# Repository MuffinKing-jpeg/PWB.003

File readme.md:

# PWB.003

PCB for powering something from 1S LI-PO or USB.  
Uses PMIC with integrated power mux.

Schematics: [Schematics](plots/PWB.003.pdf)  
Mechanical: [Mechanical](plots/PWB.003__Assembly.pdf)  
BOM: [BOM](production/bom.csv)

## Key features

- Configurable output
- Up to 3.5A input
- 2.5v\<VOUT\<16v
- Battery charging and protection
- low quiescent power consumption (In theory, still not tested)
- OVP, OCP, UVP (as claimed in datasheet for BQ24073RGT)

## Connectors

- 5x1 P1.25 for control communication with MCU
- 1x4 P2.54 for powering directly from BMS and measuring battery voltage
- 1x3 P2.00 for connecting LI-PO
- XT30 for input from battery
- XT30 for output after buck-bust
- USB-C for charging

## Key components

- BQ24073RGT
- TPS63070RNMR

## Test results

TBD

## Photos

## Disclaimer

This hardware design is provided "as is", without warranty of any kind, express or implied, including but not limited to the warranties of merchantability, fitness for a particular purpose, or noninfringement. The authors are not responsible for any damages, losses, or issues caused by the use of this design.

You are responsible for ensuring that the design complies with local regulations, safety standards, and any applicable laws.

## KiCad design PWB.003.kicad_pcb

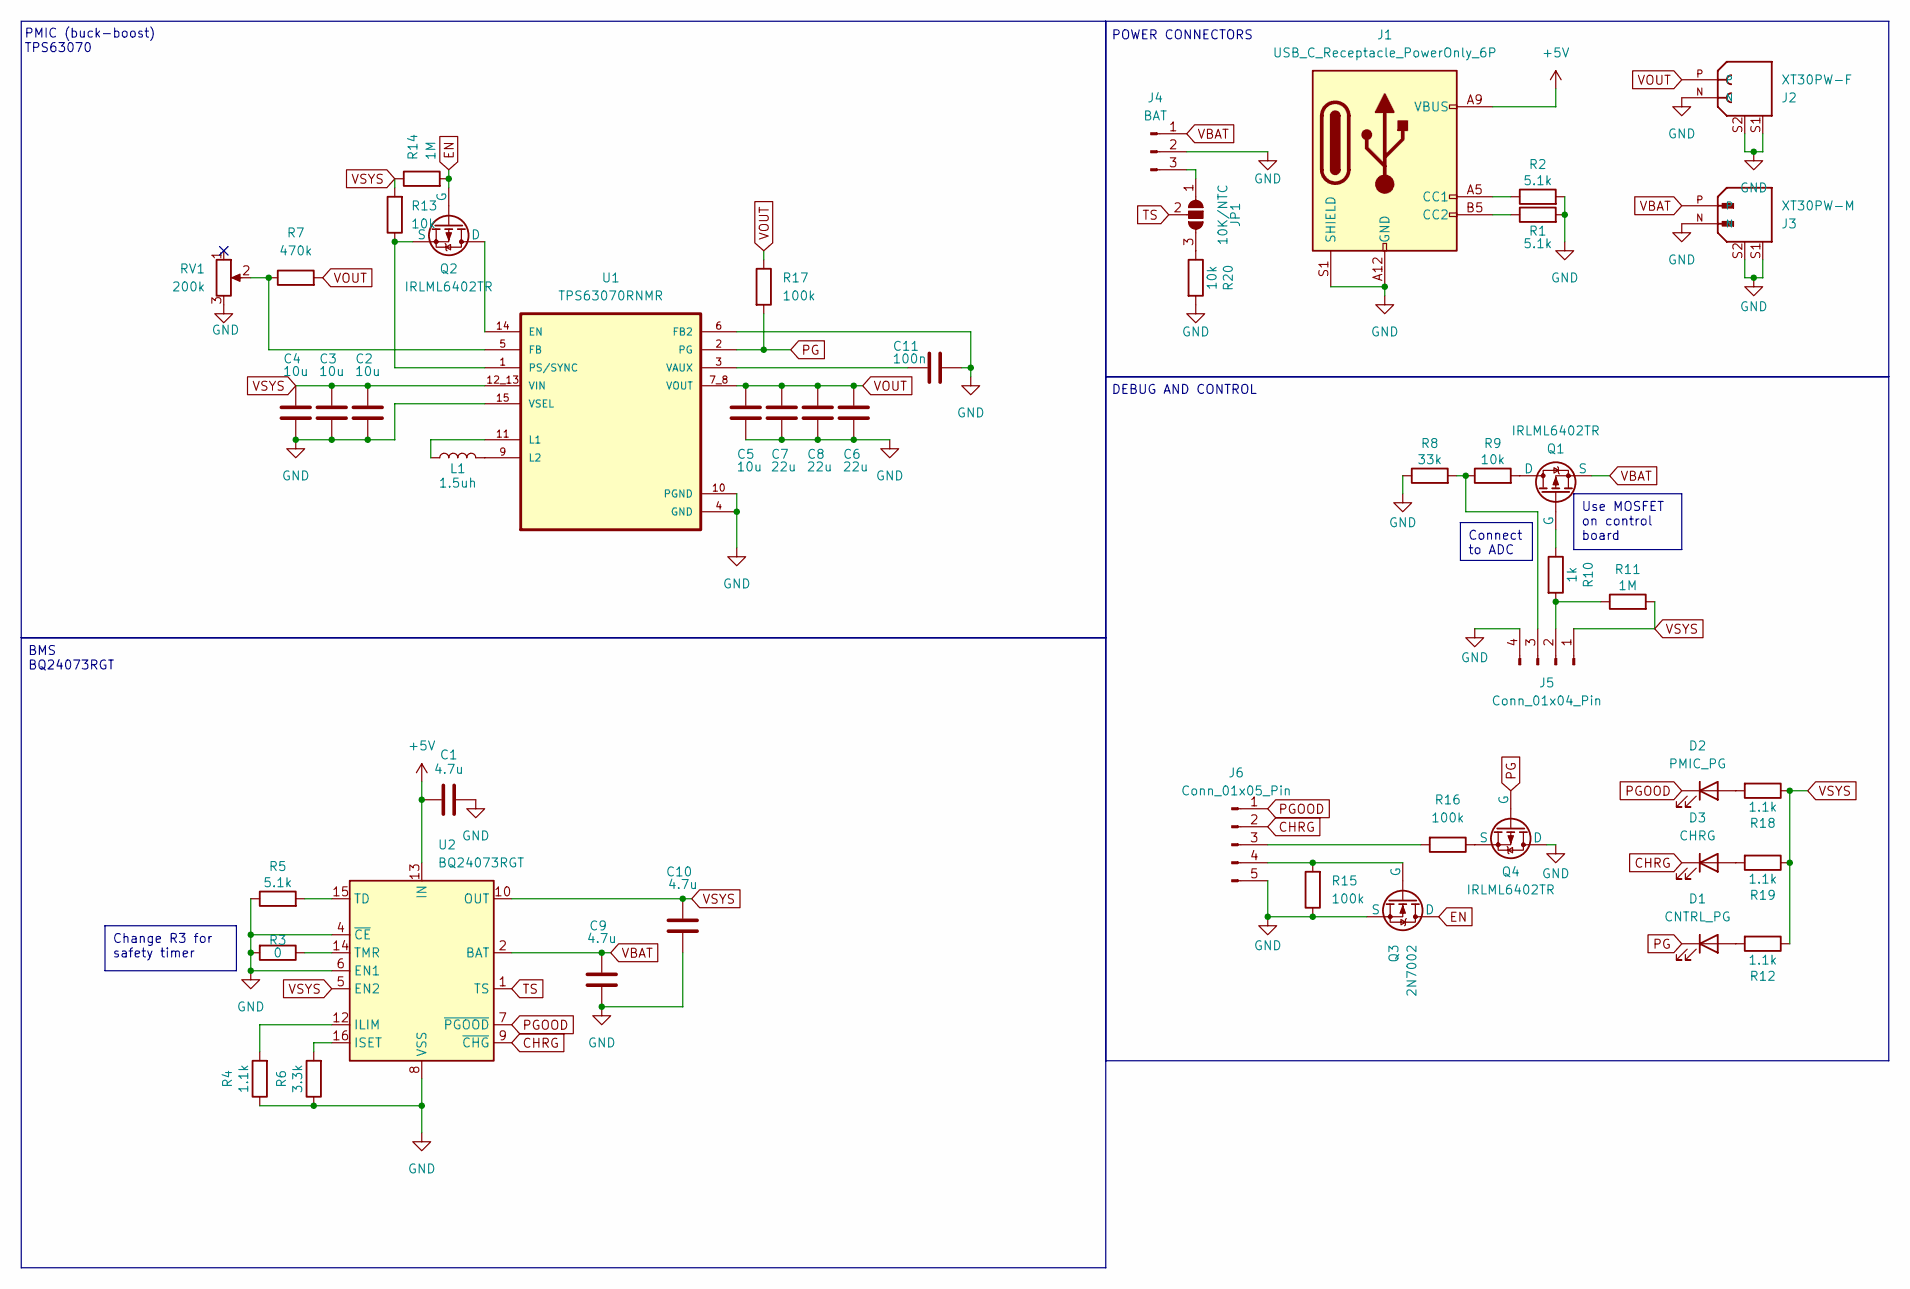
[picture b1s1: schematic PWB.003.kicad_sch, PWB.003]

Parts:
C1, C9, C10: 4.7u; C_0805_2012Metric
C2, C3, C4, C5: 10u; C_0805_2012Metric
C6, C7, C8: 22u; C_0805_2012Metric
C11: 100n; C_0805_2012Metric
D1: CNTRL_PG; LED_0805_2012Metric
D2: PMIC_PG; LED_0805_2012Metric
D3: CHRG; LED_0805_2012Metric
J1: USB_C_Receptacle_PowerOnly_6P; USB_C_Receptacle_GCT_USB4125-xx-x-0190_6P_TopMnt_Horizontal; LCSC C456012
J2: XT30PW-F; AMASS_XT30PW-F; PARTREV 1.2
J3: XT30PW-M; AMASS_XT30PW-M; PARTREV 1.2
J4: BAT; JST_PH_S3B-PH-K_1x03_P2.00mm_Horizontal; LCSC C5368765
J5: Conn_01x04_Pin; JST_EH_S4B-EH_1x04_P2.50mm_Horizontal; LCSC C5341210
J6: Conn_01x05_Pin; Hirose_DF13-05P-1.25DS_1x05_P1.25mm_Horizontal; LCSC C2689908
JP1: 10K/NTC; SolderJumper-3_P1.3mm_Open_RoundedPad1.0x1.5mm
L1: 1.5uh; L_Coilcraft_XAL4020-XXX; LCSC C3033018
Q1, Q2, Q4: IRLML6402TR; SOT-23; LCSC C347504
Q3: 2N7002; SOT-23; LCSC C8545
R1, R2, R5: 5.1k; R_0805_2012Metric
R3: 0; R_0805_2012Metric
R4, R12, R18, R19: 1.1k; R_0805_2012Metric
R6: 3.3k; R_0805_2012Metric
R7: 470k; R_0805_2012Metric
R8: 33k; R_0805_2012Metric
R9, R13, R20: 10k; R_0805_2012Metric
R10: 1k; R_0805_2012Metric
R11, R14: 1M; R_0805_2012Metric
R15, R16, R17: 100k; R_0805_2012Metric
RV1: 200k; Potentiometer_Bourns_TC33X_Vertical
U1: TPS63070RNMR; VREG_TPS63070RNMR; LCSC C109322
U2: BQ24073RGT; VQFN-16-1EP_3x3mm_P0.5mm_EP1.6x1.6mm; LCSC C15220

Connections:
+5V: C1.2, J1.A9 (VBUS), J1.B9 (VBUS), U2.13 (IN)
CHRG: D3.1 (K), J6.2, U2.9 (~CHG)
EN: Q2.2 (G), Q3.1 (D), R14.2
GND: C1.1, C2.1, C3.1, C4.1, C5.1, C6.1, C7.1, C8.1, C9.1, C10.1, C11.2, J1.A12 (GND), J1.B12 (GND), J1.S1 (SHIELD), J2.N, J2.S1, J2.S2, J3.N, J3.S1, J3.S2, J4.2, J5.4, J6.5, Q3.3 (S), Q4.1 (D), R1.2, R2.2, R3.2, R4.1, R5.1, R6.1, R8.1, R15.1, R20.2, RV1.3, U1.4 (GND), U1.6 (FB2), U1.10 (PGND), U1.15 (VSEL), U2.4 (~CE), U2.6 (EN1), U2.8 (VSS), U2.17 (VSS)
unnamed: D1.2 (A), R12.2
unnamed: D2.2 (A), R18.2
unnamed: D3.2 (A), R19.2
unnamed: J1.A5 (CC1), R2.1
unnamed: J1.B5 (CC2), R1.1
unnamed: J4.3, JP1.1 (A)
unnamed: J5.2, R10.2, R11.1
unnamed: J5.3, R8.2, R9.1
unnamed: J6.3, R16.2
unnamed: J6.4, Q3.2 (G), R15.2
unnamed: JP1.3 (B), R20.1
unnamed: Q1.1 (D), R9.2
unnamed: Q1.2 (G), R10.1
unnamed: Q2.1 (D), U1.14 (EN)
unnamed: Q2.3 (S), R13.1, U1.1 (PS/SYNC)
unnamed: Q4.3 (S), R16.1
unnamed: R7.1, RV1.2, U1.5 (FB)
unnamed: L1.1, U1.11 (L1)
unnamed: L1.2, U1.9 (L2)
unnamed: C11.1, U1.3 (VAUX)
unnamed: R4.2, U2.12 (ILIM)
unnamed: R6.2, U2.16 (ISET)
unnamed: R5.2, U2.15 (TD)
unnamed: R3.1, U2.14 (TMR)
PG: D1.1 (K), Q4.2 (G), R17.2, U1.2 (PG)
PGOOD: D2.1 (K), J6.1, U2.7 (~PGOOD)
TS: JP1.2 (C), U2.1 (TS)
VBAT: C9.2, J3.P, J4.1, Q1.3 (S), U2.2 (BAT), U2.3 (BAT)
VOUT: C5.2, C6.2, C7.2, C8.2, J2.P, R7.2, R17.1, U1.7_8 (VOUT)
VSYS: C2.2, C3.2, C4.2, C10.2, J5.1, R11.2, R12.1, R13.2, R14.1, R18.1, R19.1, U1.12_13 (VIN), U2.5 (EN2), U2.10 (OUT), U2.11 (OUT)

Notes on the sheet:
Change R3 for safety timer
Use MOSFET on control board
Connect to ADC
BMS BQ24073RGT
POWER CONNECTORS
DEBUG AND CONTROL
PMIC (buck-boost) TPS63070

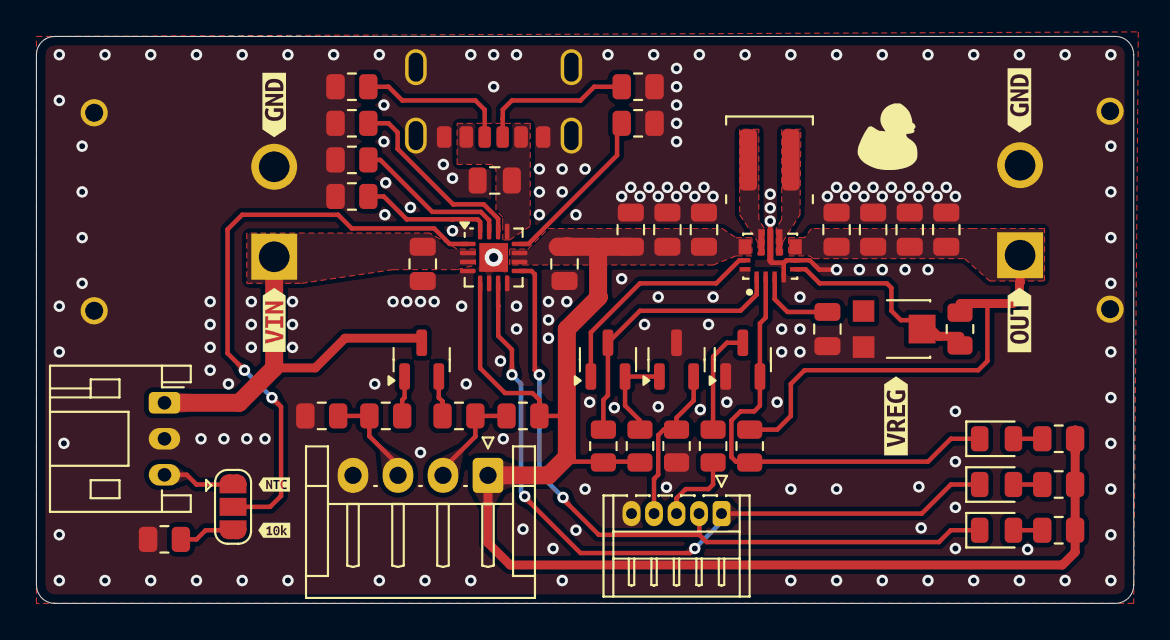
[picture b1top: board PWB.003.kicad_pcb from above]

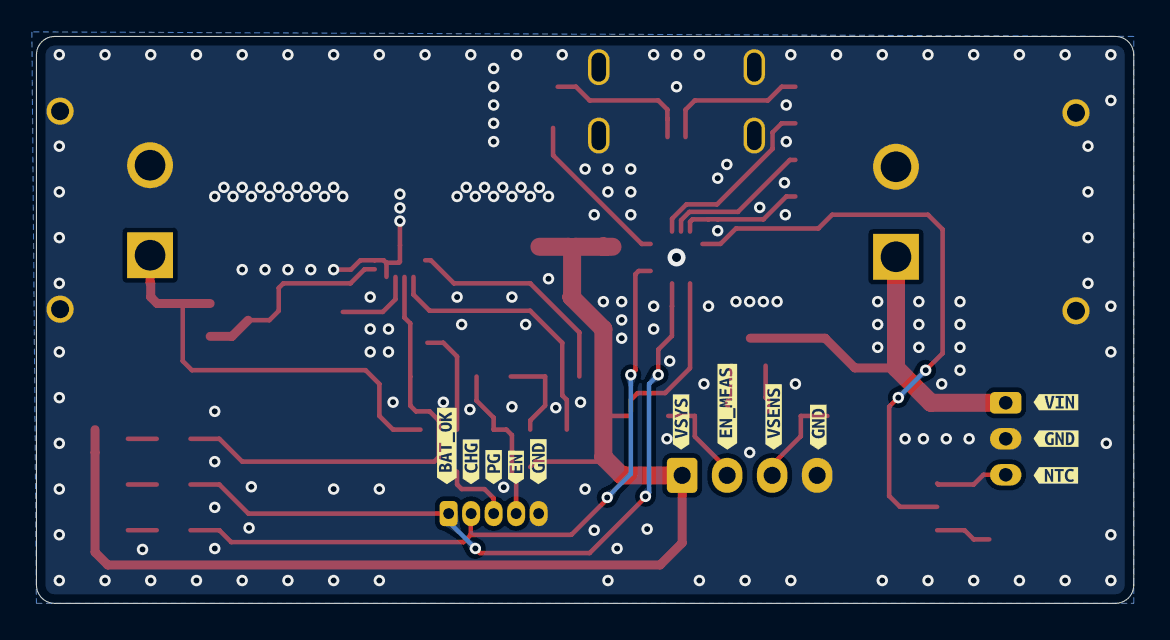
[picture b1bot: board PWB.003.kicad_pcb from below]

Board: 2 copper layers, 61.0 x 31.5 mm, 70 parts (12 on the bottom side), 34 nets.

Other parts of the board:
kibuzzard-1: G***; kibuzzard-678CDDCF
kibuzzard-2: G***; kibuzzard-678CDE28
kibuzzard-3: G***; kibuzzard-678CDB1C
kibuzzard-4: G***; kibuzzard-678CDC56
kibuzzard-5: G***; kibuzzard-678CDC37
kibuzzard-6: G***; kibuzzard-678CDC60
kibuzzard-7: G***; kibuzzard-678D5D09
kibuzzard-8: G***; kibuzzard-678CDEF3
kibuzzard-9: G***; kibuzzard-678CDEE7
kibuzzard-678D6AC8: G***; kibuzzard-678D6AC8
kibuzzard-678D6ACE: G***; kibuzzard-678D6ACE
kibuzzard-678D6AD4: G***; kibuzzard-678D6AD4
kibuzzard-678D6AE1: G***; kibuzzard-678D6AE1
kibuzzard-678D6AE6: G***; kibuzzard-678D6AE6
kibuzzard-678D6B1B: G***; kibuzzard-678D6B1B
kibuzzard-678D6B2C: G***; kibuzzard-678D6B2C
kibuzzard-678D6B8A: G***; kibuzzard-678D6B8A
kibuzzard-678D6B9C: G***; kibuzzard-678D6B9C
kibuzzard-678D6B21: G***; kibuzzard-678D6B21
kibuzzard-678D6B26: G***; kibuzzard-678D6B26
kibuzzard-678D6B93: G***; kibuzzard-678D6B93

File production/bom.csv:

Designator,Footprint,Quantity,Value,LCSC Part #
"C1, C10, C9",0805,3,4.7u,
C11,0805,1,100n,
"C2, C3, C4, C5",0805,4,10u,
"C6, C7, C8",0805,3,22u,
D1,0805,1,CNTRL_PG,
D2,0805,1,PMIC_PG,
D3,0805,1,CHRG,
J1,USB_C_Receptacle_GCT_USB4125-xx-x-0190_6P_TopMnt_Horizontal,1,USB_C_Receptacle_PowerOnly_6P,C456012
J2,AMASS_XT30PW-F,1,XT30PW-F,
J3,AMASS_XT30PW-M,1,XT30PW-M,
J4,JST_PH_S3B-PH-K_1x03_P2.00mm_Horizontal,1,BAT,C5368765
J5,JST_EH_S4B-EH_1x04_P2.50mm_Horizontal,1,Conn_01x04_Pin,C5341210
J6,Hirose_DF13-05P-1.25DS_1x05_P1.25mm_Horizontal,1,Conn_01x05_Pin,C2689908
L1,L_Coilcraft_XAL4020-XXX,1,1.5uh,C3033018
"Q1, Q2, Q4",SOT-23,3,IRLML6402TR,C347504
Q3,SOT-23,1,2N7002,C8545
"R1, R2, R5",0805,3,5.1k,
R10,0805,1,1k,
"R11, R14",0805,2,1M,
"R12, R18, R19, R4",0805,4,1.1k,
"R13, R20, R9",0805,3,10k,
"R15, R16, R17",0805,3,100k,
R3,0805,1,0,
R6,0805,1,3.3k,
R7,0805,1,470k,
R8,0805,1,33k,
RV1,Potentiometer_Bourns_TC33X_Vertical,1,200k,
U1,VREG_TPS63070RNMR,1,TPS63070RNMR,C109322
U2,VQFN-16-1EP_3x3mm_P0.5mm_EP1.6x1.6mm,1,BQ24073RGT,C15220

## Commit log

2025-01-19 Init commit
2025-01-19 Some cleanup
2025-01-19 Fixed typo
2025-01-19 Improved PCB
    - Added 10k resistor on control inputs TPS63070
    - Changed layout of inductor and filtering capacitors
    - added legend on bottom layer
    - updated DRC
    - validated design on JLCDFM
2025-01-19 Fixed bottom image
2025-03-09 Updated info - added photos
2025-03-09 Added case design files
